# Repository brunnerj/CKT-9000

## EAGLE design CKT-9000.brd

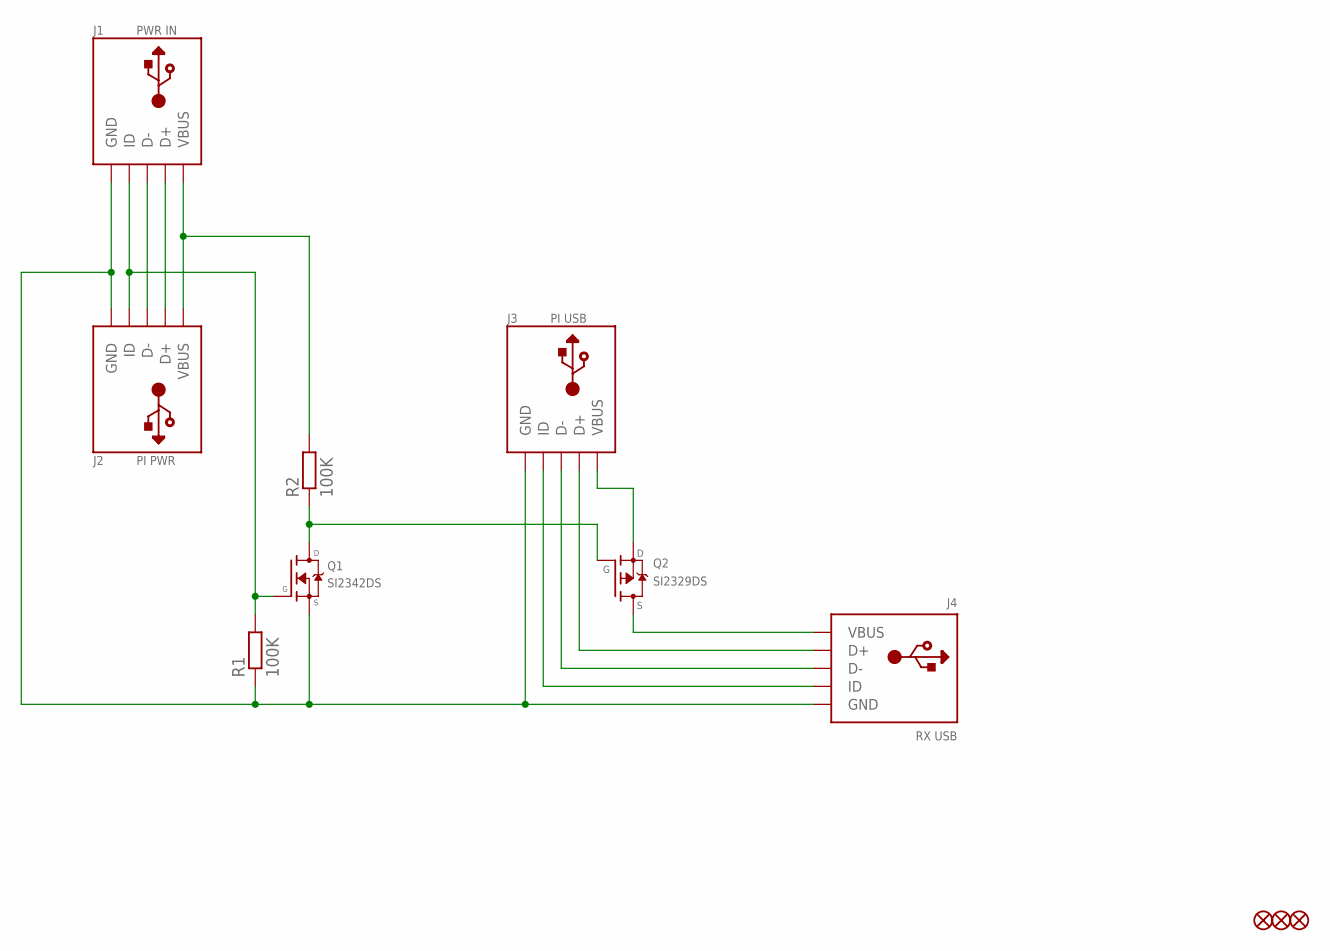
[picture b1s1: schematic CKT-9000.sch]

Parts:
FID1, FID2, FID3: FIDUCIAL""; FIDUCIAL_1MM
J1: PWR IN; GCT_USB3150
J2: PI PWR; GCT_USB3150
J3: PI USB; GCT_USB3150
J4: RX USB; AMPHENOL_10103594
Q1: SI2342DS; SOT23
Q2: SI2329DS; SOT23
R1, R2: 100K; R0805

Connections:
D+$1: J1.D+, J2.D+
D+$2: J3.D+, J4.D+
D-$1: J1.D-, J2.D-
D-$2: J3.D-, J4.D-
GND: J1.GND, J1.GND$1 (GND), J1.GND$2 (GND), J1.GND$3 (GND), J1.GND$4 (GND), J1.GND$5 (GND), J1.GND$6 (GND), J2.GND, J2.GND$1 (GND), J2.GND$2 (GND), J2.GND$3 (GND), J2.GND$4 (GND), J2.GND$5 (GND), J2.GND$6 (GND), J3.GND, J3.GND$1 (GND), J3.GND$2 (GND), J3.GND$3 (GND), J3.GND$4 (GND), J3.GND$5 (GND), J3.GND$6 (GND), J4.BASE@1 (GND), J4.BASE@2 (GND), J4.GND, J4.SPRT@1 (GND), J4.SPRT@2 (GND), J4.SPRT@3 (GND), J4.SPRT@4 (GND), Q1.2 (S), R1.1
ID$2: J3.ID, J4.ID
unnamed: Q1.3 (D), Q2.1 (G), R2.1
unnamed: J3.VBUS, Q2.2 (S)
unnamed: J1.ID, J2.ID, Q1.1 (G), R1.2
unnamed: J4.VBUS, Q2.3 (D)
VBUS$1: J1.VBUS, J2.VBUS, R2.2

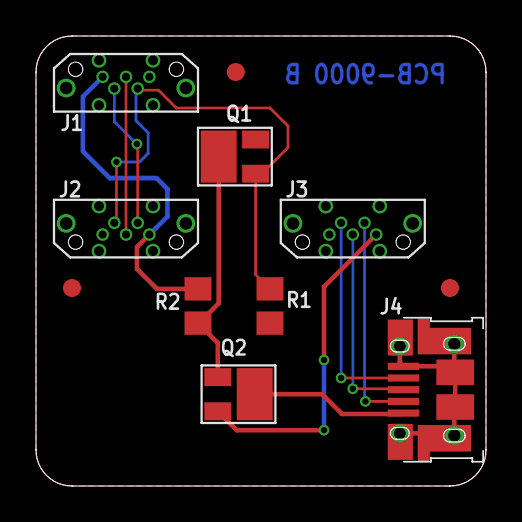
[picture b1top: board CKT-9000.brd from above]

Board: 2 copper layers, 25.0 x 25.0 mm, 12 parts (1 on the bottom side), 11 nets.

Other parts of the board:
U$1: BTS_SILK_LOGO

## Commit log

2019-11-04 Adds a MOSFET and gate bias resistor to the board. The ID pin of the PWR IN usb connector is utilized as the signal to turn the MOSFET on/off.
    Eagle Cad updated to v 9.5.1
2019-11-27 Adds a second MOSFET (p-channel) along with an additional resistor to make the circuit actually do what it is supposed to. I obviously didn't think about the prior design very thoroughly! Here's the 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
2020-03-19 Adds datasheets folder and a datasheet for the USB connector
2020-03-19 Adds the circuit BOM and updates Eagle to v9.6
